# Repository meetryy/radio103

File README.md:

bruh-SDR: **B**asic **R**adio with **U**nsoficticated **H**ardware

HF transceiver based on uSDX and BluePill board

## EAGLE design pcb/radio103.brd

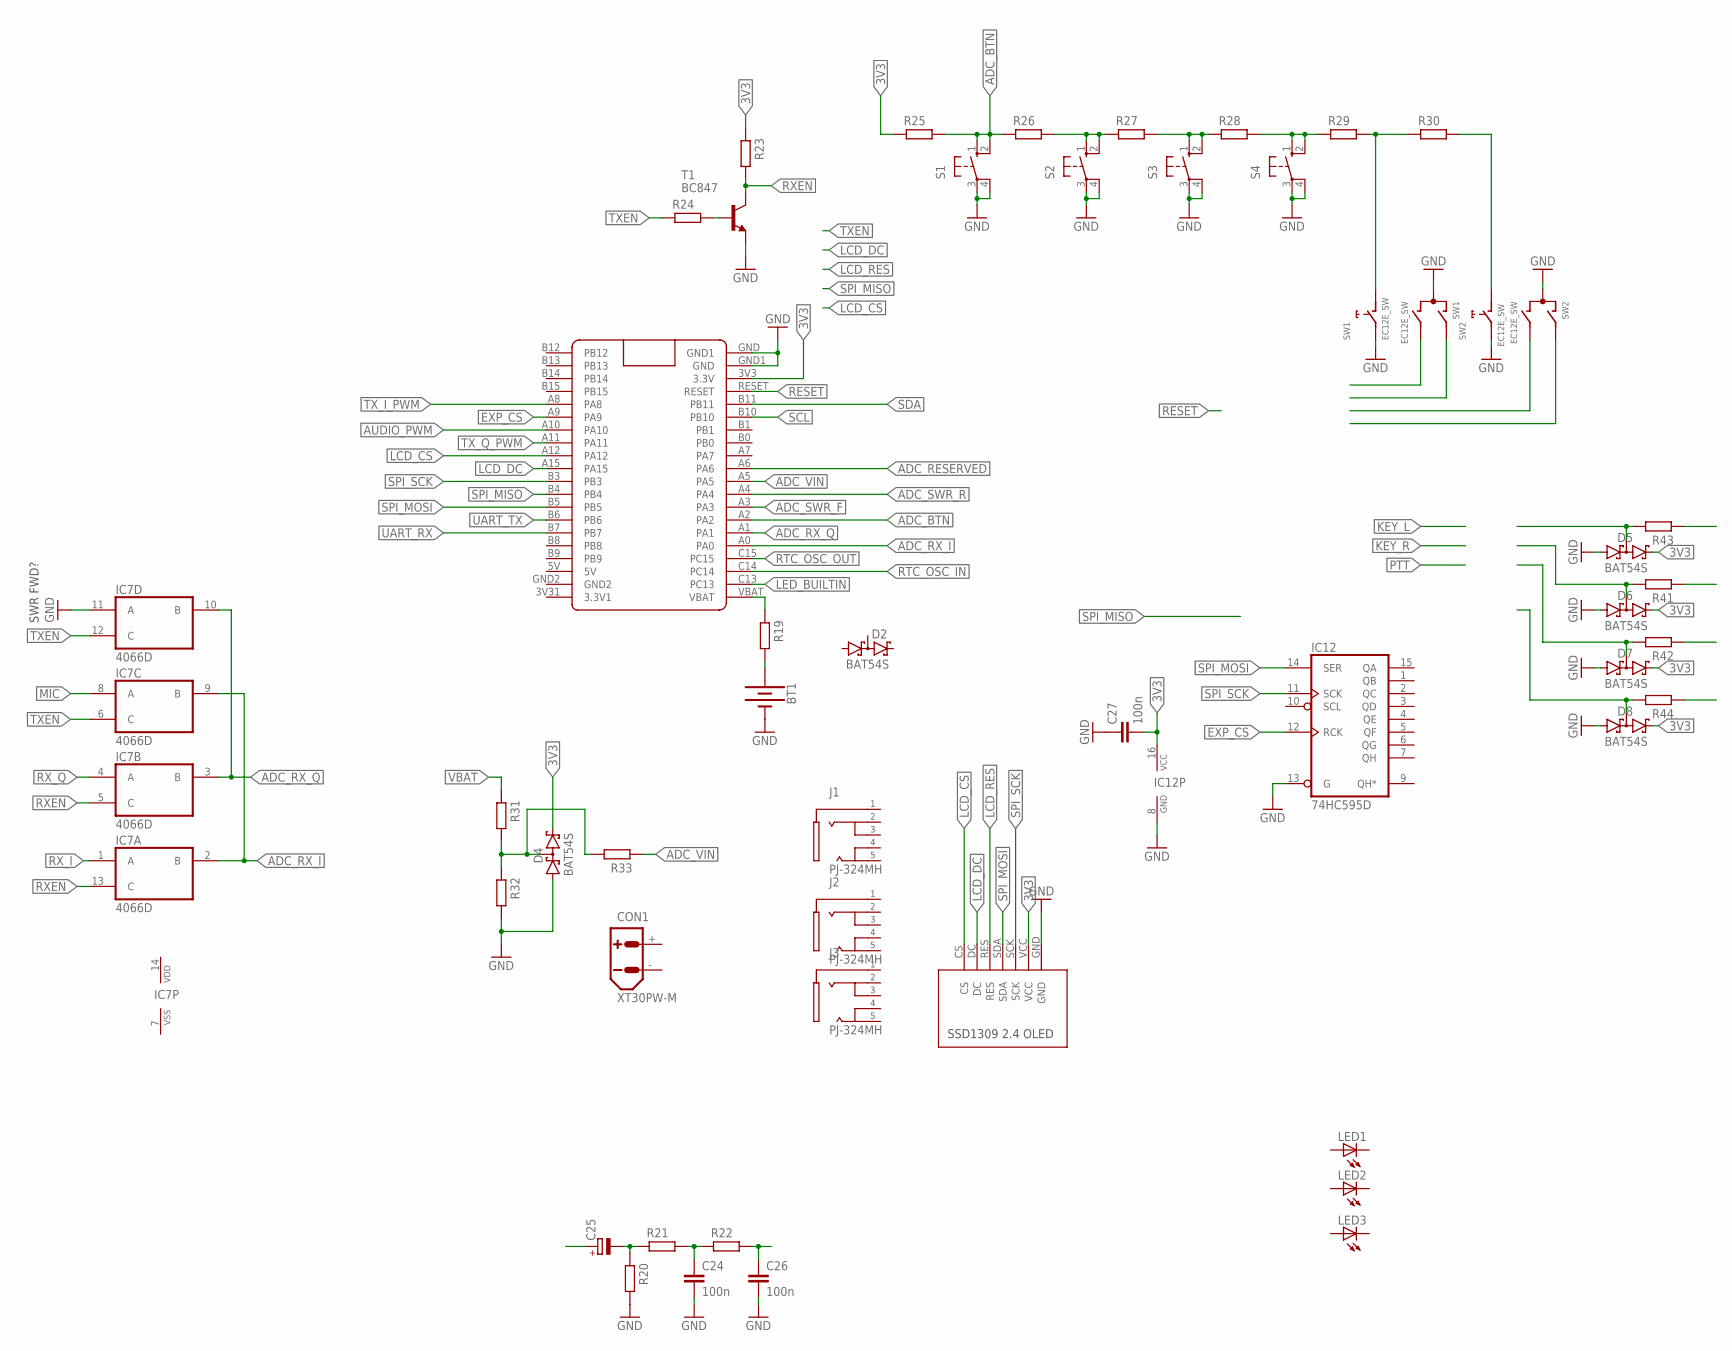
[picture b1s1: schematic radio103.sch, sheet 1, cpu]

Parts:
BT1: BATTERY-12MM_SMD; BATTCON_12MM
C24, C26, C27: 100n; C0805K
C25: CPOL-EUE2,5-6E; E2,5-6E
CON1: XT30PW-M
D2, D4, D5, D6, D7, D8: BAT54S; SOT23
IC7: 4066D; SO14
IC12: 74HC595D; SO16
J1, J2, J3: PJ-324MH
LED1, LED2, LED3: OSYG1608; C1608
R19, R20, R21, R22, R23, R24, R25, R26, R27, R28, R29, R30, R31, R32, R33, R41, R42, R43, R44: R-EU_R0805; R0805
S1, S2, S3, S4: 10-XX; B3F-10XX
SW1, SW2: EC12E_SW; ALPS_EC12E_SW
T1: BC847; SOT23
U$1: BLUE_PILL
U$4: SSD1309_2.4_OLED; SSD1309_2.42_OLED

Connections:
3V3: C27.2, D4.2 (C2), D5.2 (C2), D6.2 (C2), D7.2 (C2), D8.2 (C2), IC12.16 (VCC), R23.2, R25.2, U$1.3V3 (3.3V), U$4.VCC; also elsewhere on the board
+: CON1.+
-: CON1.-
ADC_BTN: R25.1, R26.2, S1.1 (S), S1.2 (S1), U$1.A2
ADC_RESERVED: U$1.A6
ADC_RX_I: IC7.2 (B), IC7.9 (B), U$1.A0
ADC_RX_Q: IC7.3 (B), IC7.10 (B), U$1.A1
ADC_SWR_F: U$1.A3
ADC_SWR_R: U$1.A4
ADC_VIN: R33.2, U$1.A5
AUDIO_PWM: U$1.A10
EXP_CS: IC12.12 (RCK), U$1.A9
GND: BT1.GND (-), C24.2, C26.2, C27.1, D4.1 (A1), D5.1 (A1), D6.1 (A1), D7.1 (A1), D8.1 (A1), IC7.11 (A), IC12.8 (GND), IC12.13 (G), R20.1, R32.1, S1.3, S1.4 (P1), S2.3, S2.4 (P1), S3.3, S3.4 (P1), S4.3, S4.4 (P1), SW1.C, SW1.E (2), SW2.C, SW2.E (2), T1.2 (E), U$1.GND (GND1), U$1.GND1 (GND), U$4.GND; also elsewhere on the board
LCD_CS: U$1.A12, U$4.CS
LCD_DC: U$1.A15, U$4.DC
LCD_RES: U$4.RES
LED_BUILTIN: U$1.C13
MIC: IC7.8 (A)
unnamed: C25.-, R20.2, R21.2
unnamed: C24.1, R21.1, R22.2
unnamed: C26.1, R22.1
unnamed: BT1.PWR@1 (+), R19.1
unnamed: R19.2, U$1.VBAT
unnamed: R24.1, T1.1 (B)
unnamed: R26.1, R27.2, S2.1 (S), S2.2 (S1)
unnamed: D4.3 (C1A2), R31.1, R32.2, R33.1
unnamed: R27.1, R28.2, S3.1 (S), S3.2 (S1)
unnamed: R28.1, R29.2, S4.1 (S), S4.2 (S1)
unnamed: R29.1, R30.2, SW1.D (1)
unnamed: R30.1, SW2.D (1)
unnamed: D5.3 (C1A2), R43.1
unnamed: D6.3 (C1A2), R41.1
unnamed: D7.3 (C1A2), R42.1
unnamed: D8.3 (C1A2), R44.1
RESET: U$1.RESET
RTC_OSC_IN: U$1.C14
RTC_OSC_OUT: U$1.C15
RXEN: IC7.5 (C), IC7.13 (C), R23.1, T1.3 (C)
RX_I: IC7.1 (A); also elsewhere on the board
RX_Q: IC7.4 (A); also elsewhere on the board
SCL: U$1.B10; also elsewhere on the board
SDA: U$1.B11; also elsewhere on the board
SPI_MISO: U$1.B4
SPI_MOSI: IC12.14 (SER), U$1.B5, U$4.SDA
SPI_SCK: IC12.11 (SCK), U$1.B3, U$4.SCK
TXEN: IC7.6 (C), IC7.12 (C), R24.2
TX_I_PWM: U$1.A8
TX_Q_PWM: U$1.A11
UART_RX: U$1.B7
UART_TX: U$1.B6
VBAT: R31.2
VDD: IC7.14 (VDD)
VSS: IC7.7 (VSS)

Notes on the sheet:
SWR FWD?

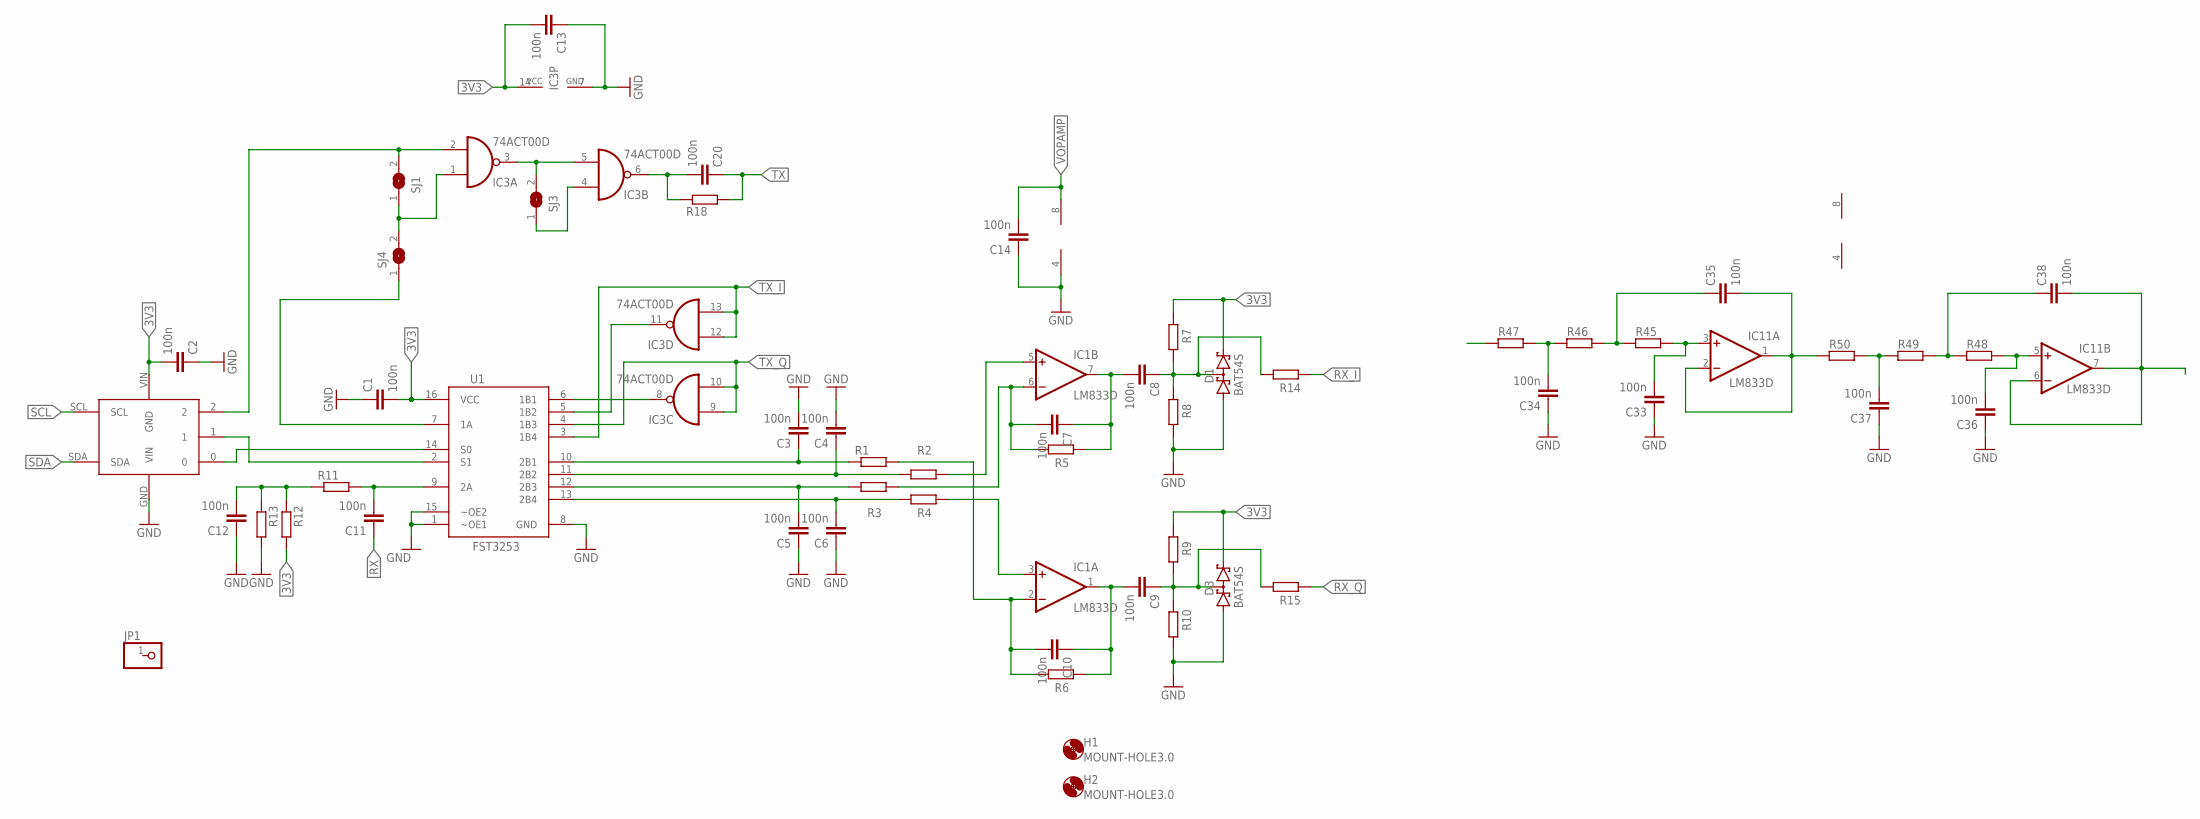
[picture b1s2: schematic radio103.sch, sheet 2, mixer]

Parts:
C1, C2, C3, C4, C5, C6, C7, C8, C9, C10, C11, C12, C13, C14, C20, C33, C34, C35, C36, C37, C38: 100n; C0805K
D1, D3: BAT54S; SOT23
H1, H2: MOUNT-HOLE3.0; 3,0
IC1, IC11: LM833D; SO08
IC3: 74ACT00D; SO14
JP1: PINHD-1X1; 1X01
R1, R2, R3, R4, R5, R6, R7, R8, R9, R10, R11, R12, R13, R14, R15, R18, R45, R46, R47, R48, R49, R50: R-EU_R0805; R0805
SJ1, SJ3, SJ4: SJ
U1: FST3253; TSSOP16L
U$2: CJMCU-5351

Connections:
3V3: C1.2, C2.2, C13.2, D1.2 (C2), D3.2 (C2), IC3.14 (VCC), R7.2, R9.2, R12.2, U1.16 (VCC), U$2.VIN (GND); also elsewhere on the board
ADC_I1: C8.1, D1.3 (C1A2), R7.1, R8.2, R14.1
ADC_Q1: C9.1, D3.3 (C1A2), R9.1, R10.2, R15.1
GND: C1.1, C2.1, C3.2, C4.2, C5.1, C6.1, C12.1, C13.1, C14.1, C33.1, C34.1, C36.1, C37.1, D1.1 (A1), D3.1 (A1), IC1.4 (V-), IC3.7 (GND), R8.1, R10.1, R13.2, U1.1 (~OE1), U1.8 (GND), U1.15 (~OE2), U$2.GND (VIN); also elsewhere on the board
unnamed: C3.1, R1.1, U1.10 (2B1)
unnamed: C4.1, R2.1, U1.11 (2B2)
unnamed: C5.2, R3.1, U1.12 (2B3)
unnamed: C6.2, R4.1, U1.13 (2B4)
unnamed: C10.2, IC1.2 (-IN), R1.2, R6.1
unnamed: IC1.5 (+IN), R2.2
unnamed: C7.2, IC1.6 (-IN), R3.2, R5.1
unnamed: IC1.3 (+IN), R4.2
unnamed: C9.2, C10.1, IC1.1 (OUT), R6.2
unnamed: C7.1, C8.2, IC1.7 (OUT), R5.2
unnamed: C11.2, R11.2, U1.9 (2A)
unnamed: U1.2 (S1), U$2.1
unnamed: C12.2, R11.1, R12.1, R13.1
unnamed: U1.14 (S0), U$2.0
unnamed: IC3.8 (O), U1.6 (1B1)
unnamed: IC3.11 (O), U1.5 (1B2)
unnamed: IC3.2 (I1), SJ1.2, U$2.2
unnamed: IC3.1 (I0), SJ1.1, SJ4.2
unnamed: IC3.3 (O), IC3.5 (I1), SJ3.2
unnamed: IC3.4 (I0), SJ3.1
unnamed: C20.2, IC3.6 (O), R18.1
unnamed: SJ4.1, U1.7 (1A)
unnamed: C33.2, IC11.3 (+IN), R45.2
unnamed: C35.1, R45.1, R46.2
unnamed: C35.2, IC11.1 (OUT), IC11.2 (-IN), R50.1
unnamed: C38.1, R48.1, R49.2
unnamed: C34.2, R46.1, R47.2
unnamed: C37.2, R49.1, R50.2
unnamed: C36.2, IC11.5 (+IN), R48.2
unnamed: C38.2, IC11.6 (-IN), IC11.7 (OUT)
RX: C11.1
RX_I: R14.2; also elsewhere on the board
RX_Q: R15.2; also elsewhere on the board
SCL: U$2.SCL; also elsewhere on the board
SDA: U$2.SDA; also elsewhere on the board
TX: C20.1, R18.2
TX_I: IC3.12 (I0), IC3.13 (I1), U1.3 (1B4)
TX_Q: IC3.9 (I0), IC3.10 (I1), U1.4 (1B3)
V+: IC11.8 (V+)
V-: IC11.4 (V-)
VOPAMP: C14.2, IC1.8 (V+); also elsewhere on the board

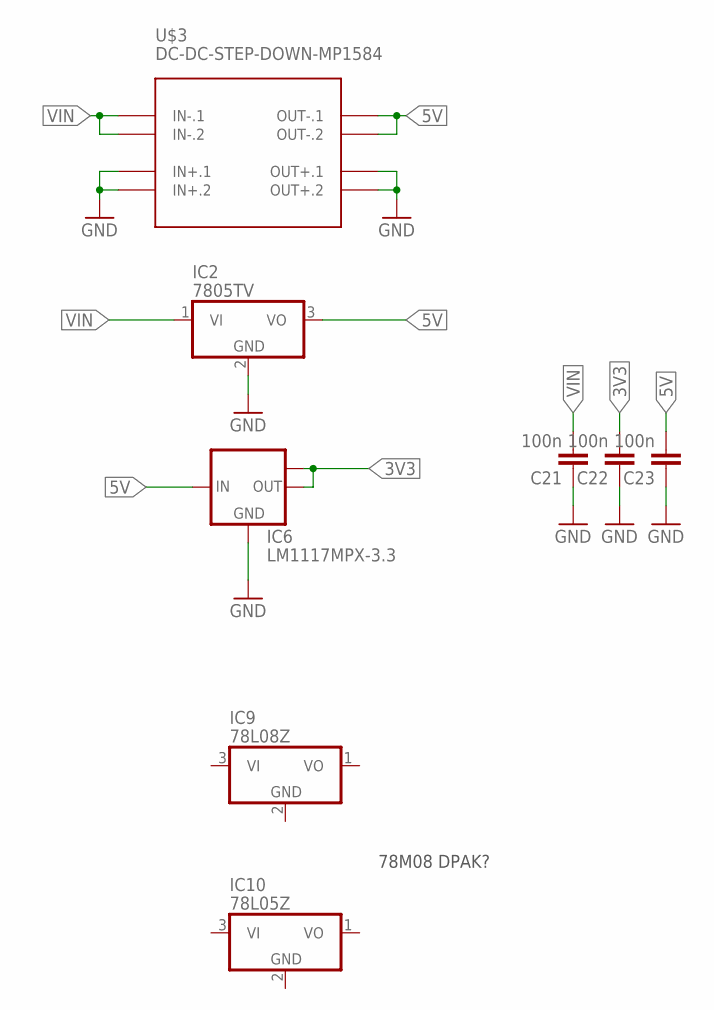
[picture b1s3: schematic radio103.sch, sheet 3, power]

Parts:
C21, C22, C23: 100n; C0805K
IC2: 7805TV; TO220V
IC6: LM1117MPX-3.3; SOT223
IC9: 78L08Z; TO92
IC10: 78L05Z; TO92
U$3: DC-DC-STEP-DOWN-MP1584

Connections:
3V3: C22.2, IC6.2 (OUT), IC6.TAB (OUT1); also elsewhere on the board
5V: C23.2, IC2.3 (VO), IC6.3 (IN), U$3.OUT-.1, U$3.OUT-.2; also elsewhere on the board
GND: C21.1, C22.1, C23.1, IC2.2 (GND), IC6.1 (GND), U$3.IN+.1, U$3.IN+.2, U$3.OUT+.1, U$3.OUT+.2; also elsewhere on the board
VIN: C21.2, IC2.1 (VI), U$3.IN-.1, U$3.IN-.2

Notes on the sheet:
78M08 DPAK?

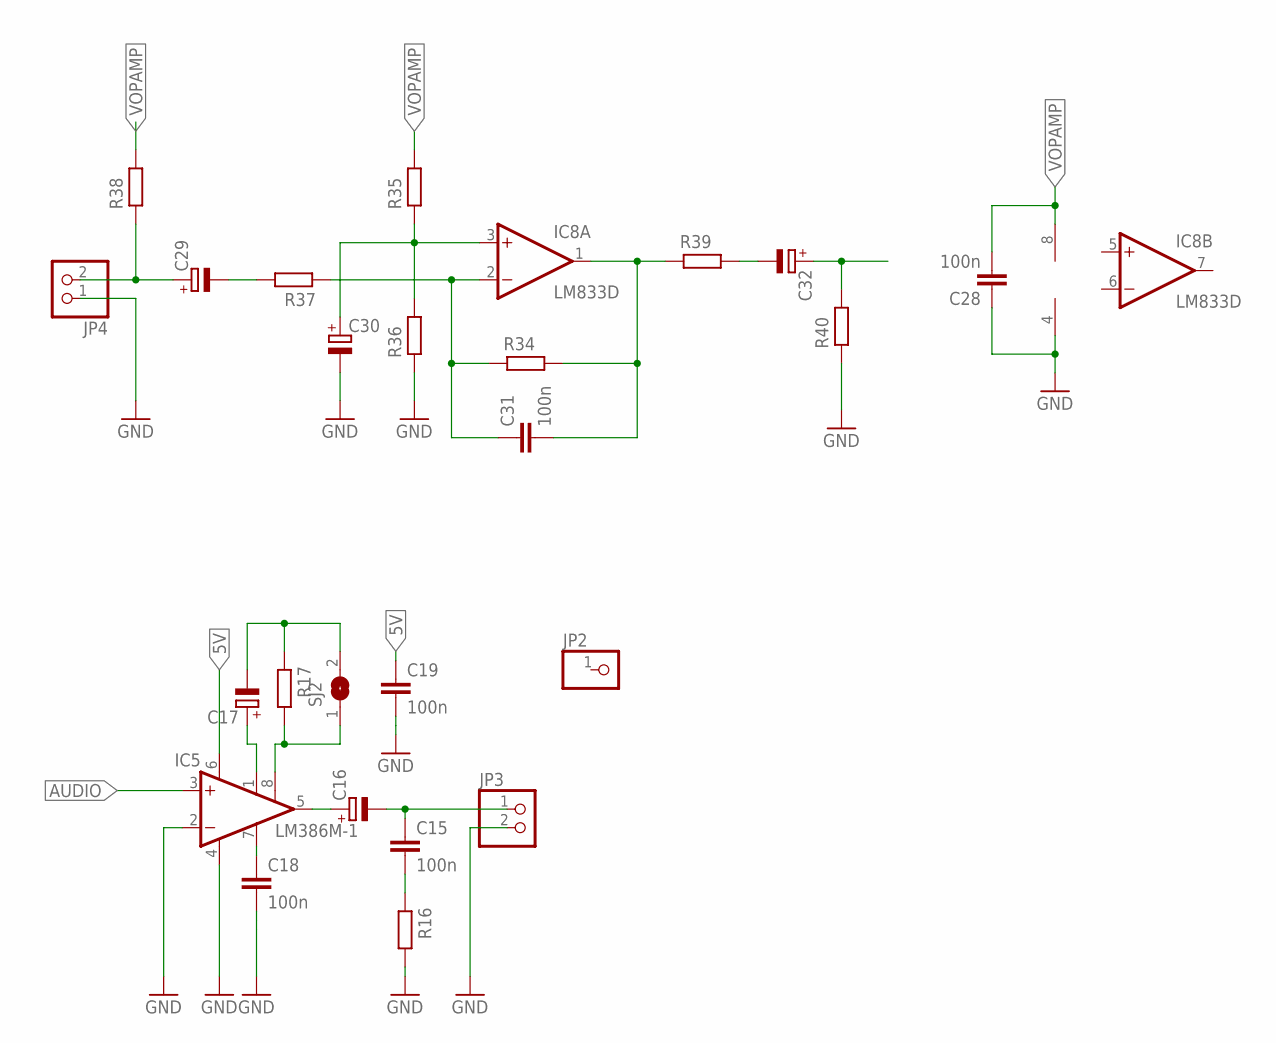
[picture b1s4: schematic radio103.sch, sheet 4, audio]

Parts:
C15, C18, C19, C28, C31: 100n; C0805K
C16, C17, C29, C30, C32: CPOL-EUE2,5-6E; E2,5-6E
IC5: LM386M-1; SO08
IC8: LM833D; SO08
JP2: PINHD-1X1; 1X01
JP3, JP4: PINHD-1X2; 1X02
R16, R17, R34, R35, R36, R37, R38, R39, R40: R-EU_R0805; R0805
SJ2: SJ

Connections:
5V: C19.1, IC5.6 (VS); also elsewhere on the board
AUDIO: IC5.3 (+IN)
GND: C18.2, C19.2, C28.1, C30.-, IC5.2 (-IN), IC5.4 (GND), IC8.4 (V-), JP3.2, JP4.1, R16.1, R36.2, R40.2; also elsewhere on the board
unnamed: C17.+, IC5.1 (GAIN)
unnamed: IC5.8 (GAIN), R17.1, SJ2.1
unnamed: C17.-, R17.2, SJ2.2
unnamed: C18.1, IC5.7 (BYPASS)
unnamed: C16.+, IC5.5 (OUT)
unnamed: C15.1, C16.-, JP3.1
unnamed: C15.2, R16.2
unnamed: C30.+, IC8.3 (+IN), R35.2, R36.1
unnamed: C31.1, IC8.2 (-IN), R34.2, R37.2
unnamed: C31.2, IC8.1 (OUT), R34.1, R39.2
unnamed: C29.-, R37.1
unnamed: C29.+, JP4.2, R38.2
unnamed: C32.-, R39.1
unnamed: C32.+, R40.1
VOPAMP: C28.2, IC8.8 (V+), R35.1, R38.1; also elsewhere on the board

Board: 2 copper layers, 140 parts (120 on the bottom side), 85 nets, no tracks yet.

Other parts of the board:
H3, H4, H5: MOUNT-HOLE3.0; 3,0

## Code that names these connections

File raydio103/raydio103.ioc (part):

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Mcu.Name=STM32F103C(8-B)Tx
Mcu.Package=LQFP48
Mcu.UserName=STM32F103C8Tx
PA0-WKUP.GPIOParameters=GPIO_Label
PA0-WKUP.GPIO_Label=ADC_RX_I
PA0-WKUP.Signal=ADCx_IN0
PA1.GPIOParameters=GPIO_Label
PA1.GPIO_Label=ADC_RX_Q
PA1.Signal=ADCx_IN1
PA10.GPIOParameters=GPIO_Label
PA10.GPIO_Label=AUDIO_PWM
PA10.Signal=S_TIM1_CH3
PA11.GPIOParameters=GPIO_Label
PA11.GPIO_Label=TX_Q_PWM
PA11.Signal=S_TIM1_CH4
PA12.GPIOParameters=GPIO_Speed,PinState,GPIO_PuPd,GPIO_Label
PA12.GPIO_Label=PIN_LCD_CS_2
PA12.GPIO_PuPd=GPIO_PULLUP
PA12.GPIO_Speed=GPIO_SPEED_FREQ_HIGH
PA12.PinState=GPIO_PIN_RESET
PA12.Signal=GPIO_Output
PA13.Mode=Serial_Wire
PA13.Signal=SYS_JTMS-SWDIO
PA14.Mode=Serial_Wire
PA14.Signal=SYS_JTCK-SWCLK
PA15.GPIOParameters=GPIO_Speed,GPIO_PuPd,GPIO_Label
PA15.GPIO_Label=PIN_LCD_DC
PA15.GPIO_PuPd=GPIO_PULLDOWN
PA15.GPIO_Speed=GPIO_SPEED_FREQ_HIGH
PA15.Signal=GPIO_Output
PA2.Signal=ADCx_IN2
PA3.Signal=ADCx_IN3
PA4.Signal=ADCx_IN4
PA5.Signal=ADCx_IN5
PA8.GPIOParameters=GPIO_Label
PA8.GPIO_Label=TX_Q_PWM
PA8.Signal=S_TIM1_CH1
PA9.GPIOParameters=GPIO_Label
PA9.GPIO_Label=PIN_CS_EXT
PA9.Signal=GPIO_Output
PB10.Mode=I2C
PB10.Signal=I2C2_SCL
PB11.Mode=I2C
PB11.Signal=I2C2_SDA
PB15.Signal=GPIO_Output
PB3.Mode=Full_Duplex_Master
PB3.Signal=SPI1_SCK
PB4.Mode=Full_Duplex_Master
PB4.Signal=SPI1_MISO
PB5.Mode=Full_Duplex_Master
PB5.Signal=SPI1_MOSI
PB6.Mode=Asynchronous
PB6.Signal=USART1_TX
PB7.Mode=Asynchronous
PB7.Signal=USART1_RX
PB8.Signal=GPIO_Output
PB9.Signal=GPIO_Output
PC13-TAMPER-RTC.GPIOParameters=GPIO_Label
PC13-TAMPER-RTC.GPIO_Label=LED_BUILTIN
PC13-TAMPER-RTC.Signal=GPIO_Output
PC14-OSC32_IN.Mode=LSE-External-Oscillator
PC14-OSC32_IN.Signal=RCC_OSC32_IN
PC15-OSC32_OUT.Mode=LSE-External-Oscillator
PC15-OSC32_OUT.Signal=RCC_OSC32_OUT
PD0-OSC_IN.Mode=HSE-External-Oscillator
PD0-OSC_IN.Signal=RCC_OSC_IN
PD1-OSC_OUT.Mode=HSE-External-Oscillator
PD1-OSC_OUT.Signal=RCC_OSC_OUT
RCC.SYSCLKFreq_VALUE=128000000
RCC.SYSCLKSource=RCC_SYSCLKSOURCE_PLLCLK
board=custom

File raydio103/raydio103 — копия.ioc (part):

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Mcu.Name=STM32F103C(8-B)Tx
Mcu.Package=LQFP48
Mcu.UserName=STM32F103C8Tx
PA0-WKUP.GPIOParameters=GPIO_Label
PA0-WKUP.GPIO_Label=ADC_RX_I
PA0-WKUP.Signal=ADCx_IN0
PA1.GPIOParameters=GPIO_Label
PA1.GPIO_Label=ADC_RX_Q
PA1.Signal=ADCx_IN1
PA10.GPIOParameters=GPIO_Label
PA10.GPIO_Label=AUDIO_PWM
PA10.Signal=S_TIM1_CH3
PA11.GPIOParameters=GPIO_Label
PA11.GPIO_Label=TX_Q_PWM
PA11.Signal=S_TIM1_CH4
PA13.Mode=Serial_Wire
PA13.Signal=SYS_JTMS-SWDIO
PA14.Mode=Serial_Wire
PA14.Signal=SYS_JTCK-SWCLK
PA2.GPIOParameters=GPIO_Label
PA2.GPIO_Label=ADC_MIC
PA2.Signal=ADCx_IN2
PA3.GPIOParameters=GPIO_Label
PA3.GPIO_Label=ADC_BTN
PA3.Signal=ADCx_IN3
PA8.GPIOParameters=GPIO_Label
PA8.GPIO_Label=TX_I_PWM
PA8.Signal=S_TIM1_CH1
PB10.GPIOParameters=GPIO_Label,GPIO_Speed,GPIO_PuPd
PB10.GPIO_Label=PIN_LCD_CS
PB10.GPIO_PuPd=GPIO_PULLDOWN
PB10.GPIO_Speed=GPIO_SPEED_FREQ_HIGH
PB10.Signal=GPIO_Output
PB3.Mode=Full_Duplex_Master
PB3.Signal=SPI1_SCK
PB4.Mode=Full_Duplex_Master
PB4.Signal=SPI1_MISO
PB5.Mode=Full_Duplex_Master
PB5.Signal=SPI1_MOSI
PB6.Mode=Asynchronous
PB6.Signal=USART1_TX
PB7.Mode=Asynchronous
PB7.Signal=USART1_RX
PB8.Mode=I2C
PB8.Signal=I2C1_SCL
PB9.Mode=I2C
PB9.Signal=I2C1_SDA
PC13-TAMPER-RTC.GPIOParameters=GPIO_Speed,GPIO_PuPd,GPIO_Label,GPIO_ModeDefaultOutputPP
PC13-TAMPER-RTC.GPIO_Label=PIN_LED
PC13-TAMPER-RTC.GPIO_ModeDefaultOutputPP=GPIO_MODE_OUTPUT_OD
PC13-TAMPER-RTC.GPIO_PuPd=GPIO_NOPULL
PC13-TAMPER-RTC.GPIO_Speed=GPIO_SPEED_FREQ_HIGH
PC13-TAMPER-RTC.Signal=GPIO_Output
PC14-OSC32_IN.Mode=LSE-External-Oscillator
PC14-OSC32_IN.Signal=RCC_OSC32_IN
PC15-OSC32_OUT.Mode=LSE-External-Oscillator
PC15-OSC32_OUT.Signal=RCC_OSC32_OUT
PD0-OSC_IN.Mode=HSE-External-Oscillator
PD0-OSC_IN.Signal=RCC_OSC_IN
PD1-OSC_OUT.Mode=HSE-External-Oscillator
PD1-OSC_OUT.Signal=RCC_OSC_OUT
RCC.SYSCLKFreq_VALUE=128000000
RCC.SYSCLKSource=RCC_SYSCLKSOURCE_PLLCLK
board=custom

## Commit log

2022-06-25 DSP works!~~
2022-06-26 DSP works, FFT doesnt
2022-06-30 AGC + soft clipper
2022-07-06 MCP23S17 + CD4066 + decimation works!
    don't use remapped SPI1 w/ I2C1!
2022-07-07 MCP encoder + mic amp
2022-07-08 fonts + font generator + UI layout
2022-07-13 graphics
2022-07-25 SSD1309 DMA works
2022-07-27 gfx improved
2022-07-31 menu system, correct fonts, RLE splash creator
2022-08-07 menu system + splash RLE
2022-08-08 test

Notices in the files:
parts and their libraries:
diy-modules: Released under the Creative Commons Attribution 4.0 International License: http://creativecommons.org/licenses/by/4.0
SparkFun-Batteries: Licensing: Creative Commons ShareAlike 4.0 International - https://creativecommons.org/licenses/by-sa/4.0
